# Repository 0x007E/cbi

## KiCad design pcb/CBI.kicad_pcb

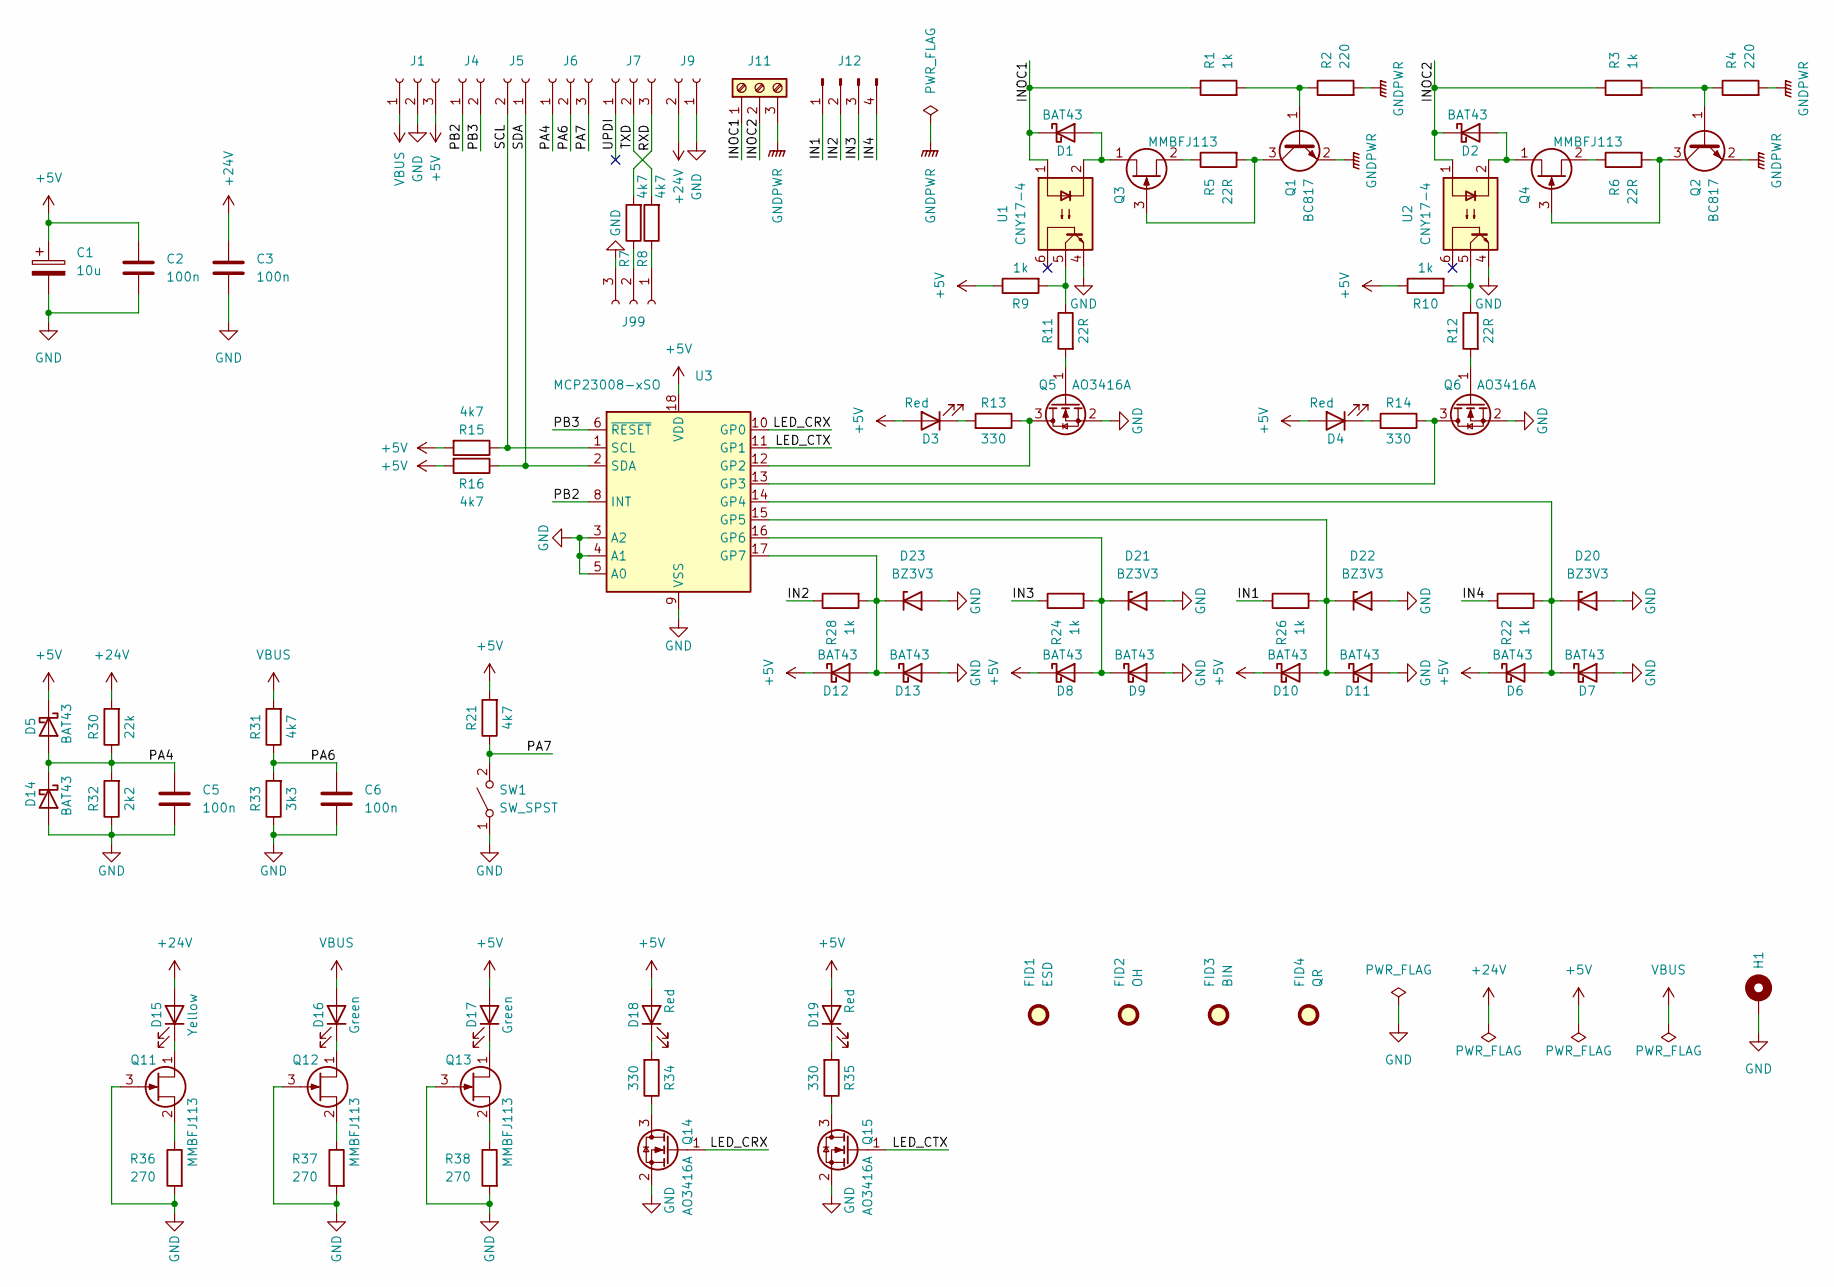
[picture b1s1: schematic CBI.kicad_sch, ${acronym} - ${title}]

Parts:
C1: 10u; CP_EIA-3528-21_Kemet-B
C2, C3, C5, C6: 100n; C_1206_3216Metric
D1, D2, D5, D6, D7, D8, D9, D10, D11, D12, D13, D14: BAT43; D_MiniMELF
D3, D4, D18, D19: Red; LED_1206_3216Metric
D15: Yellow; LED_1206_3216Metric
D16, D17: Green; LED_1206_3216Metric
D20, D21, D22, D23: BZ3V3; D_MiniMELF
FID1: ESD; ESD-Logo_6.6x6mm_SilkScreen
FID2: OH; OSHW-Logo_5.7x6mm_SilkScreen
FID3: BIN; WEEE-Logo_4.2x6mm_SilkScreen
FID4: QR; QR_0x007e_very_small
H1: MountingHole_Pad; MountingHole_3.2mm_M3_DIN965_Pad
J1, J6, J7, J99: Conn_01x03_Socket; PinSocket_1x03_P2.54mm_Vertical; DigiKey 2057-RS1-03-G-ND
J4, J5, J9: Conn_01x02_Socket; PinSocket_1x02_P2.54mm_Vertical; DigiKey 2057-RS1-02-G-ND
J11: Screw_Terminal_01x03; PhoenixContact_MSTBVA_2,5_3-G-5,08_1x03_P5.08mm_Vertical; DigiKey 277-1151-ND, 277-1012-ND
J12: Conn_01x04_Pin; PinHeader_1x04_P2.54mm_Vertical
Q1, Q2: BC817; SOT-23
Q3, Q4, Q11, Q12, Q13: MMBFJ113; SOT-23; DigiKey MMBFJ113CT-ND
Q5, Q6, Q14, Q15: AO3416A; SOT-23
R1, R3, R9, R10, R22, R24, R26, R28: 1k; R_1206_3216Metric
R2, R4: 220; R_1206_3216Metric
R5, R6, R11, R12: 22R; R_1206_3216Metric
R7, R8, R15, R16, R21, R31: 4k7; R_1206_3216Metric
R13, R14, R34, R35: 330; R_1206_3216Metric
R30: 22k; R_1206_3216Metric
R32: 2k2; R_1206_3216Metric
R33: 3k3; R_1206_3216Metric
R36, R37, R38: 270; R_1206_3216Metric
SW1: SW_SPST; SW_SPST_PTS645
U1, U2: CNY17-4; SMDIP-6_W9.53mm; DigiKey 160-1323-5-ND
U3: MCP23008-xSO; SOIC-18W_7.5x11.6mm_P1.27mm; DigiKey MCP23008-E/SO-ND

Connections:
+5V: C1.1, C2.1, D3.2 (A), D4.2 (A), D5.1 (K), D6.1 (K), D8.1 (K), D10.1 (K), D12.1 (K), D17.2 (A), D18.2 (A), D19.2 (A), J1.3, R9.1, R10.1, R15.2, R16.2, R21.2, U3.18 (VDD)
+24V: C3.1, D15.2 (A), J9.2, R30.2
/IN1: J12.1, R26.1
/IN2: J12.2, R28.1
/IN3: J12.3, R24.1
/IN4: J12.4, R22.1
/INOC1: D1.1 (K), J11.1, R1.1, U1.1
/INOC2: D2.1 (K), J11.2, R3.1, U2.1
/LED_CRX: Q14.1 (G), U3.10 (GP0)
/LED_CTX: Q15.1 (G), U3.11 (GP1)
/PA4: C5.1, D5.2 (A), D14.1 (K), J6.1, R30.1, R32.2
/PA6: C6.1, J6.2, R31.1, R33.2
/PA7: J6.3, R21.1, SW1.2 (B)
/PB2: J4.1, U3.8 (INT)
/PB3: J4.2, U3.6 (~RESET)
/RXD: J7.3, R7.2
/SCL: J5.2, R15.1, U3.1 (SCL)
/SDA: J5.1, R16.1, U3.2 (SDA)
/TXD: J7.2, R8.2
/UPDI: J7.1
GND: C1.2, C2.2, C3.2, C5.2, C6.2, D7.2 (A), D9.2 (A), D11.2 (A), D13.2 (A), D14.2 (A), D20.2 (A), D21.2 (A), D22.2 (A), D23.2 (A), H1.1, J1.2, J9.1, J99.3, Q5.2 (S), Q6.2 (S), Q11.3 (G), Q12.3 (G), Q13.3 (G), Q14.2 (S), Q15.2 (S), R32.1, R33.1, R36.2, R37.2, R38.2, SW1.1 (A), U1.4, U2.4, U3.3 (A2), U3.4 (A1), U3.5 (A0), U3.9 (VSS)
GNDPWR: J11.3, Q1.2 (E), Q2.2 (E), R2.2, R4.2
unnamed: D1.2 (A), Q3.1 (D), U1.2
unnamed: D2.2 (A), Q4.1 (D), U2.2
unnamed: D3.1 (K), R13.2
unnamed: D4.1 (K), R14.2
unnamed: D10.2 (A), D11.1 (K), D22.1 (K), R26.2, U3.15 (GP5)
unnamed: D12.2 (A), D13.1 (K), D23.1 (K), R28.2, U3.17 (GP7)
unnamed: D15.1 (K), Q11.1 (D)
unnamed: D16.1 (K), Q12.1 (D)
unnamed: D17.1 (K), Q13.1 (D)
unnamed: D18.1 (K), R34.2
unnamed: D19.1 (K), R35.2
unnamed: D6.2 (A), D7.1 (K), D20.1 (K), R22.2, U3.14 (GP4)
unnamed: D8.2 (A), D9.1 (K), D21.1 (K), R24.2, U3.16 (GP6)
unnamed: J99.1, R8.1
unnamed: J99.2, R7.1
unnamed: Q1.1 (B), R1.2, R2.1
unnamed: Q1.3 (C), Q3.3 (G), R5.2
unnamed: Q2.1 (B), R3.2, R4.1
unnamed: Q2.3 (C), Q4.3 (G), R6.2
unnamed: Q3.2 (S), R5.1
unnamed: Q4.2 (S), R6.1
unnamed: Q5.3 (D), R13.1, U3.12 (GP2)
unnamed: Q5.1 (G), R11.2
unnamed: Q6.3 (D), R14.1, U3.13 (GP3)
unnamed: Q6.1 (G), R12.2
unnamed: Q11.2 (S), R36.1
unnamed: Q12.2 (S), R37.1
unnamed: Q13.2 (S), R38.1
unnamed: Q14.3 (D), R34.1
unnamed: Q15.3 (D), R35.1
unnamed: R10.2, R12.1, U2.5
unnamed: R9.2, R11.1, U1.5
VBUS: D16.2 (A), J1.1, R31.2

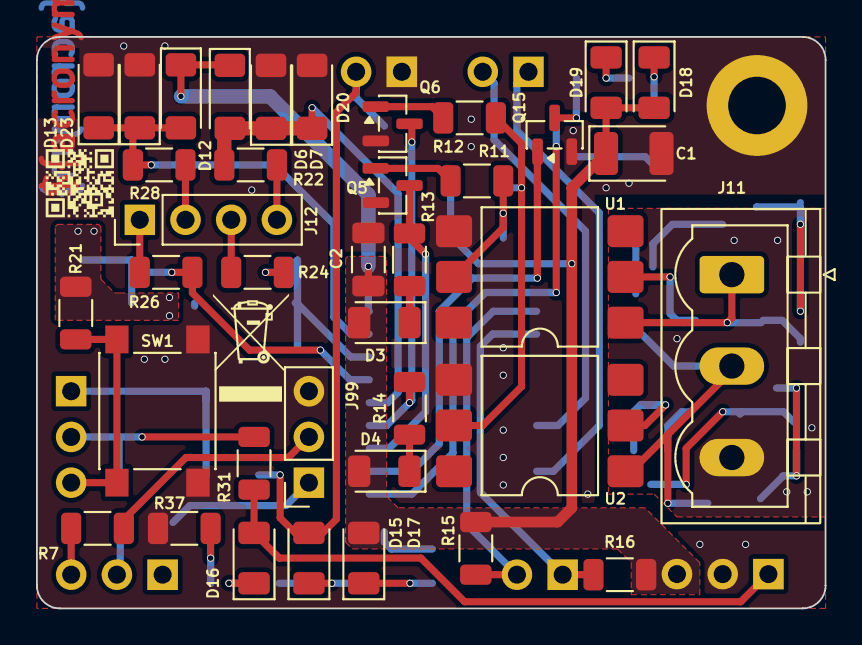
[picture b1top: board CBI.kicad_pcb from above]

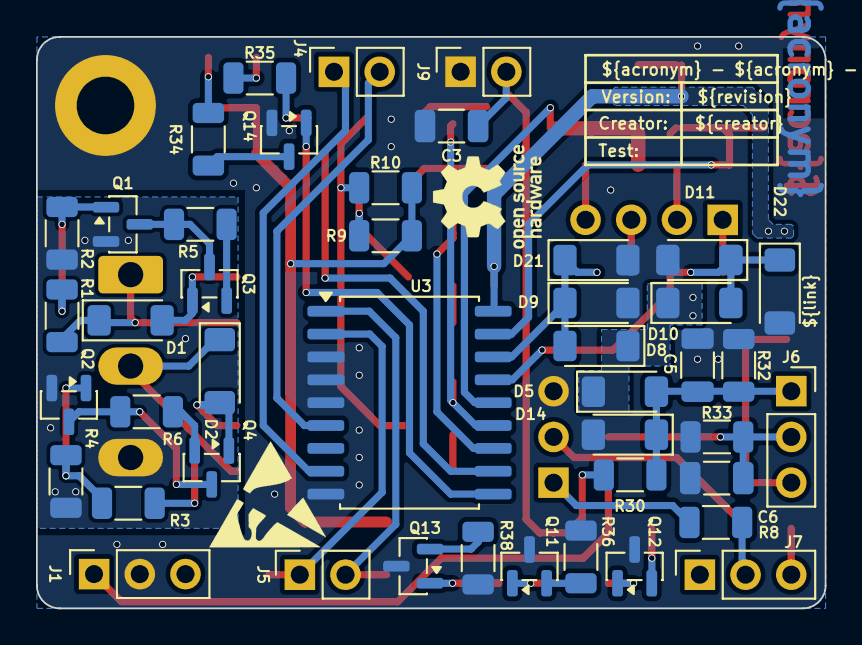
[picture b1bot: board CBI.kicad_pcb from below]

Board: 2 copper layers, 43.8 x 31.8 mm, 87 parts (46 on the bottom side), 54 nets.

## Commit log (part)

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2026-05-21 Add pcb layout
2026-05-21 Add missing vendor(id)

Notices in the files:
parts and their libraries:
license: CC BY-NC-SA 4.0
